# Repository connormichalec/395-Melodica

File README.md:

# 395-Melodica

Current setup, Key decoding (and to midi) on the smaller stm chip, looping jankily combined on bigger stm chip that was originally just going to be used for synthesis. Smaller ship sends midi data to synthesis. Synthesis manages looping and sends back midi data for smaller one to route to the output. TODO: Either re-seperate using a smaller chip with bigger ram (ideal). Or just get rid of smaller one together.

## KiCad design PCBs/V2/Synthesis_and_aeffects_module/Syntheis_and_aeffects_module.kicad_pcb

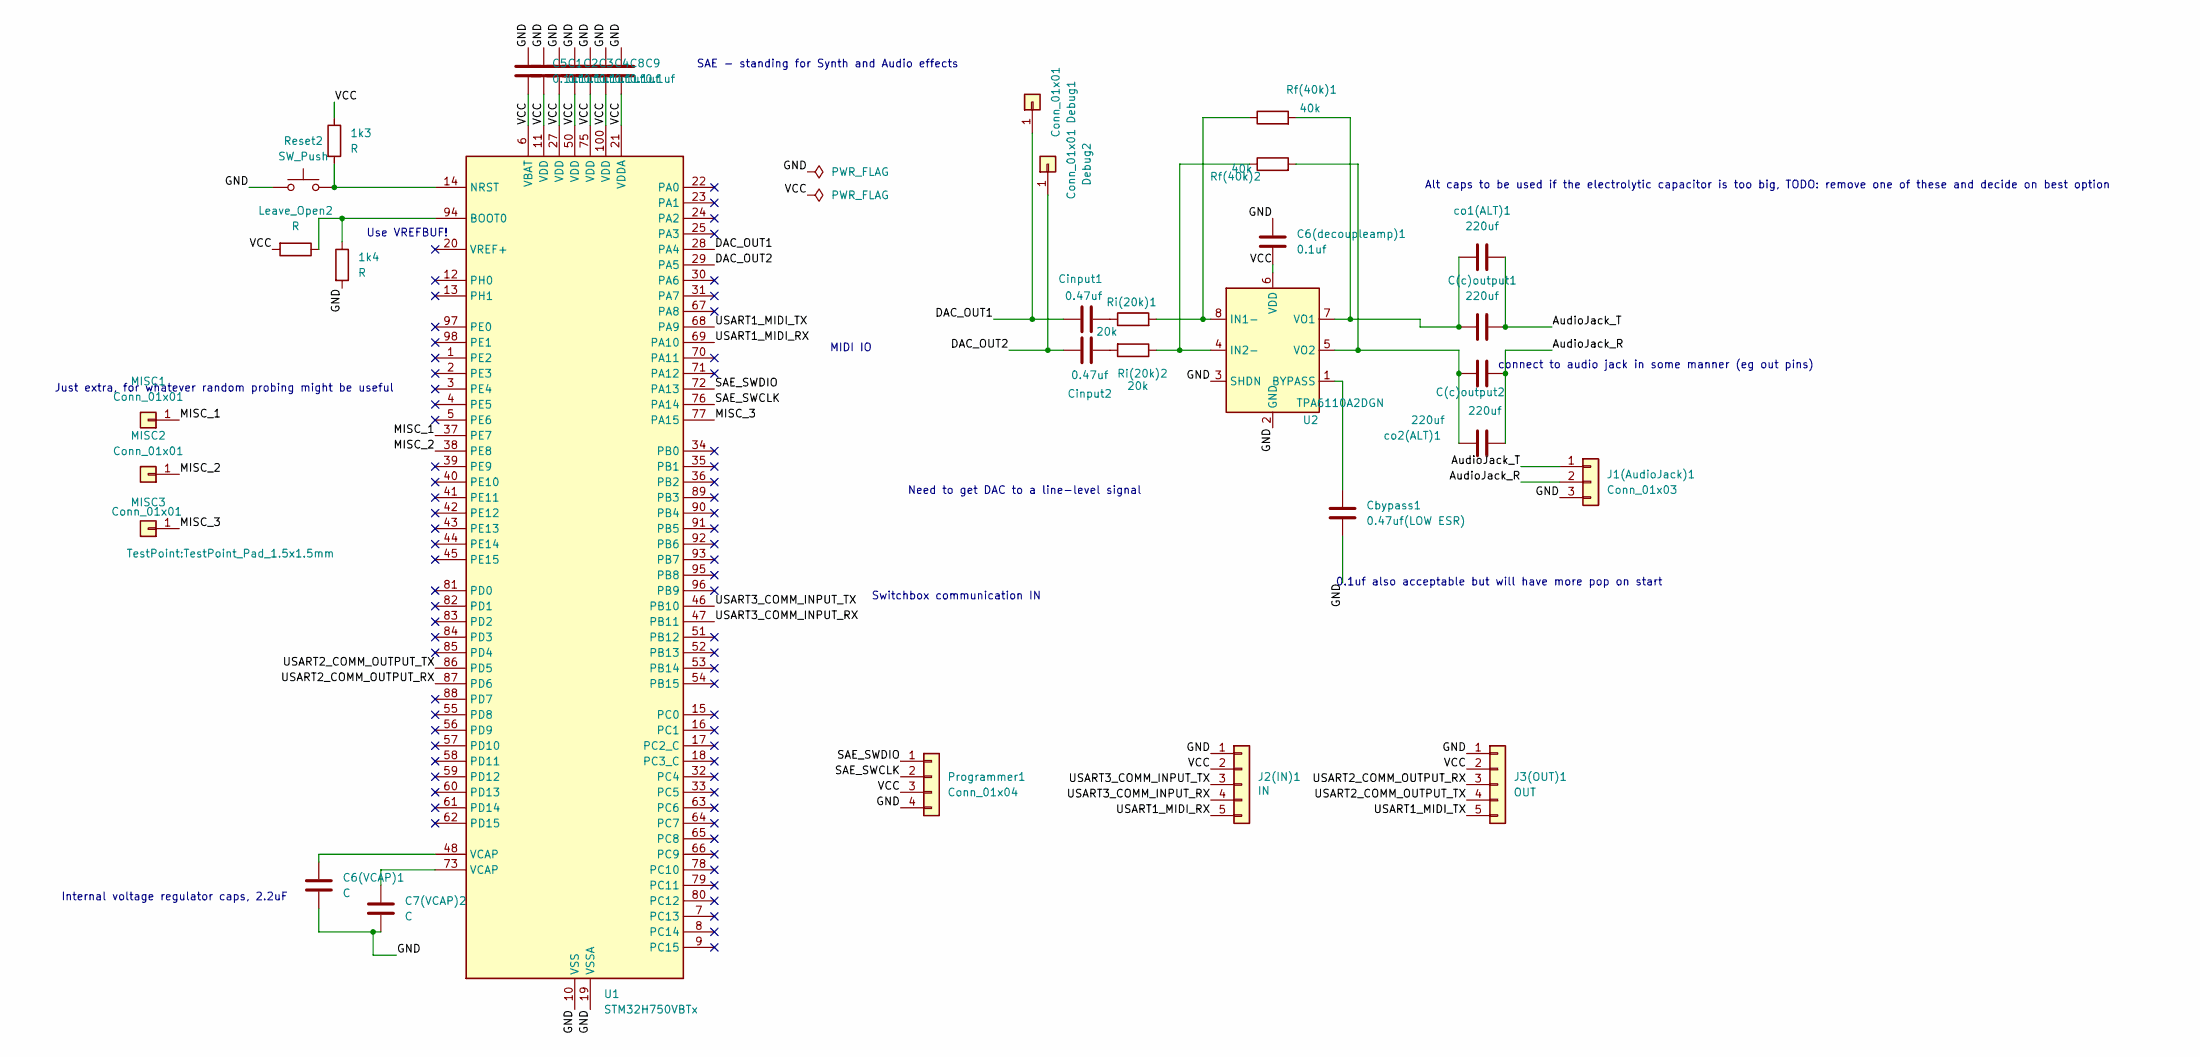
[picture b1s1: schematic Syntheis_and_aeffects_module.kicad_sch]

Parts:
1k3, 1k4: R; R_0603_1608Metric_Pad0.98x0.95mm_HandSolder
C1, C2, C3, C4, C5, C6(decoupleamp)1, C8, C9: 0.1uf; C_0603_1608Metric_Pad1.08x0.95mm_HandSolder
C6(VCAP)1, C7(VCAP)2: C; C_0603_1608Metric_Pad1.08x0.95mm_HandSolder
C(c)output1, C(c)output2: 220uf; CP_Radial_D5.0mm_P2.00mm
Cbypass1: 0.47uf(LOW ESR); C_0603_1608Metric_Pad1.08x0.95mm_HandSolder
Cinput1, Cinput2: 0.47uf; C_0603_1608Metric_Pad1.08x0.95mm_HandSolder
Debug1, Debug2: Conn_01x01; TestPoint_Pad_1.5x1.5mm
J1(AudioJack)1: Conn_01x03; PinHeader_1x03_P2.54mm_Vertical
J2(IN)1: IN; PinHeader_1x05_P2.54mm_Vertical
J3(OUT)1: OUT; PinHeader_1x05_P2.54mm_Vertical
Leave_Open2: R; R_Axial_DIN0204_L3.6mm_D1.6mm_P7.62mm_Horizontal
MISC1, MISC2, MISC3: Conn_01x01; TestPoint_Pad_1.5x1.5mm
Programmer1: Conn_01x04; PinHeader_1x04_P2.54mm_Vertical
Reset2: SW_Push; SW_PUSH_6mm_H4.3mm
Rf(40k)1, Rf(40k)2: 40k; R_Axial_DIN0207_L6.3mm_D2.5mm_P10.16mm_Horizontal
Ri(20k)1, Ri(20k)2: 20k; R_Axial_DIN0207_L6.3mm_D2.5mm_P10.16mm_Horizontal
U1: STM32H750VBTx; LQFP-100_14x14mm_P0.5mm
U2: TPA6110A2DGN; HVSSOP-8-1EP_3x3mm_P0.65mm_EP1.57x1.89mm
co1(ALT)1, co2(ALT)1: 220uf; C_1206_3216Metric_Pad1.33x1.80mm_HandSolder

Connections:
/AudioJack_R: C(c)output2.2, J1(AudioJack)1.2, co2(ALT)1.2
/AudioJack_T: C(c)output1.2, J1(AudioJack)1.1, co1(ALT)1.2
/DAC_OUT1: Cinput1.1, Debug1.1, U1.28 (PA4)
/DAC_OUT2: Cinput2.1, Debug2.1, U1.29 (PA5)
/GND: 1k4.2, C1.1, C2.1, C3.1, C4.1, C5.1, C6(VCAP)1.2, C6(decoupleamp)1.1, C7(VCAP)2.2, C8.1, C9.1, Cbypass1.2, J1(AudioJack)1.3, J2(IN)1.1, J3(OUT)1.1, Programmer1.4, Reset2.1, U1.10 (VSS), U1.19 (VSSA), U1.26 (VSS), U1.49 (VSS), U1.74 (VSS), U1.99 (VSS), U2.2 (GND), U2.3 (SHDN), U2.9 (GND)
/MISC_1: MISC1.1, U1.37 (PE7)
/MISC_2: MISC2.1, U1.38 (PE8)
/MISC_3: MISC3.1, U1.77 (PA15)
/SAE_SWCLK: Programmer1.2, U1.76 (PA14)
/SAE_SWDIO: Programmer1.1, U1.72 (PA13)
/USART1_MIDI_RX: J2(IN)1.5, U1.69 (PA10)
/USART1_MIDI_TX: J3(OUT)1.5, U1.68 (PA9)
/USART2_COMM_OUTPUT_RX: J3(OUT)1.3, U1.87 (PD6)
/USART2_COMM_OUTPUT_TX: J3(OUT)1.4, U1.86 (PD5)
/USART3_COMM_INPUT_RX: J2(IN)1.4, U1.47 (PB11)
/USART3_COMM_INPUT_TX: J2(IN)1.3, U1.46 (PB10)
/VCC: 1k3.1, C1.2, C2.2, C3.2, C4.2, C5.2, C6(decoupleamp)1.2, C8.2, C9.2, J2(IN)1.2, J3(OUT)1.2, Leave_Open2.2, Programmer1.3, U1.6 (VBAT), U1.11 (VDD), U1.21 (VDDA), U1.27 (VDD), U1.50 (VDD), U1.75 (VDD), U1.100 (VDD), U2.6 (VDD)
unnamed: C6(VCAP)1.1, U1.48 (VCAP)
unnamed: C7(VCAP)2.1, U1.73 (VCAP)
unnamed: Cinput1.2, Ri(20k)1.1
unnamed: Cinput2.2, Ri(20k)2.2
unnamed: 1k4.1, Leave_Open2.1, U1.94 (BOOT0)
unnamed: 1k3.2, Reset2.2, U1.14 (NRST)
unnamed: Cbypass1.1, U2.1 (BYPASS)
unnamed: Rf(40k)1.1, Ri(20k)1.2, U2.8 (IN1-)
unnamed: Rf(40k)2.1, Ri(20k)2.1, U2.4 (IN2-)
unnamed: C(c)output1.1, Rf(40k)1.2, U2.7 (VO1), co1(ALT)1.1
unnamed: C(c)output2.1, Rf(40k)2.2, U2.5 (VO2), co2(ALT)1.1

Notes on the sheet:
Switchbox communication IN
Need to get DAC to a line-level signal
connect to audio jack in some manner (eg out pins)
0.1uf also acceptable but will have more pop on start
SAE - standing for Synth and Audio effects
MIDI IO
Internal voltage regulator caps, 2.2uF
Alt caps to be used if the electrolytic capacitor is too big, TODO: remove one of these and decide on best option
Use VREFBUF!
Just extra, for whatever random probing might be useful

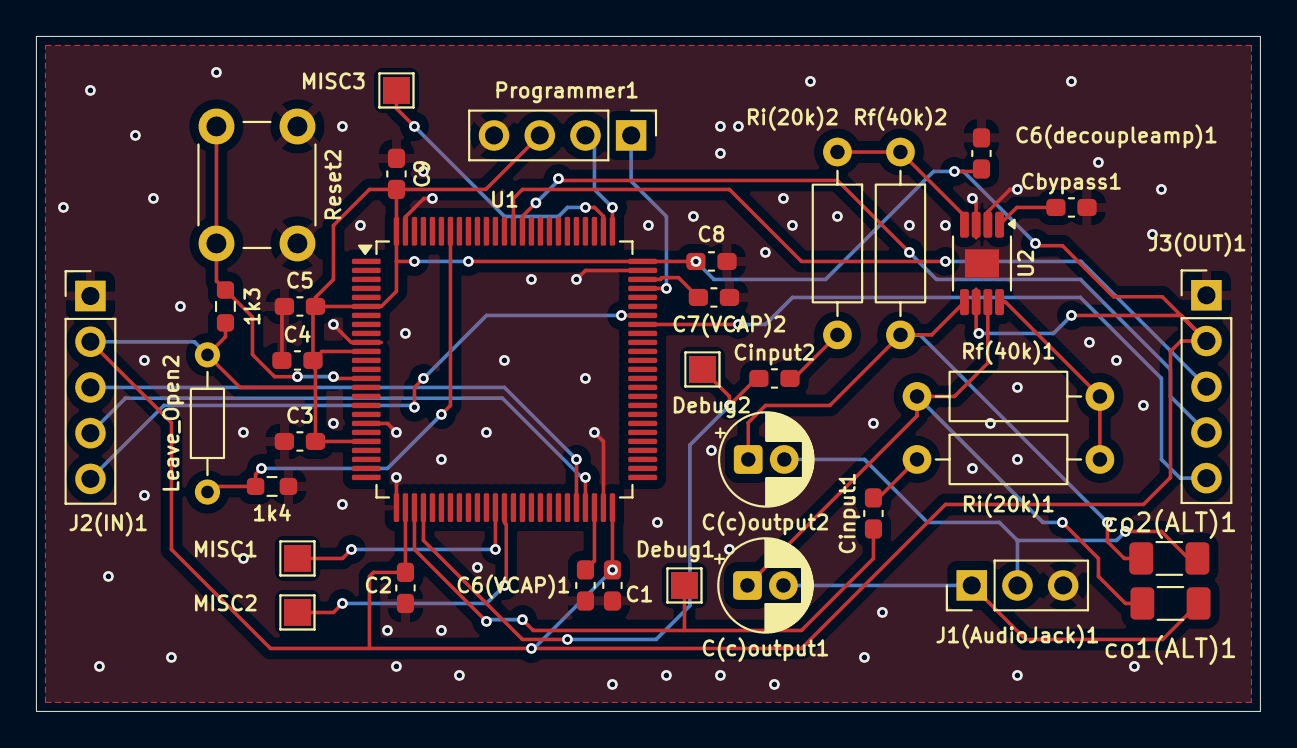
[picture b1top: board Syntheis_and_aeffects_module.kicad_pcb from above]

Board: 2 copper layers, 68.0 x 37.5 mm, 36 parts (0 on the bottom side), 28 nets.

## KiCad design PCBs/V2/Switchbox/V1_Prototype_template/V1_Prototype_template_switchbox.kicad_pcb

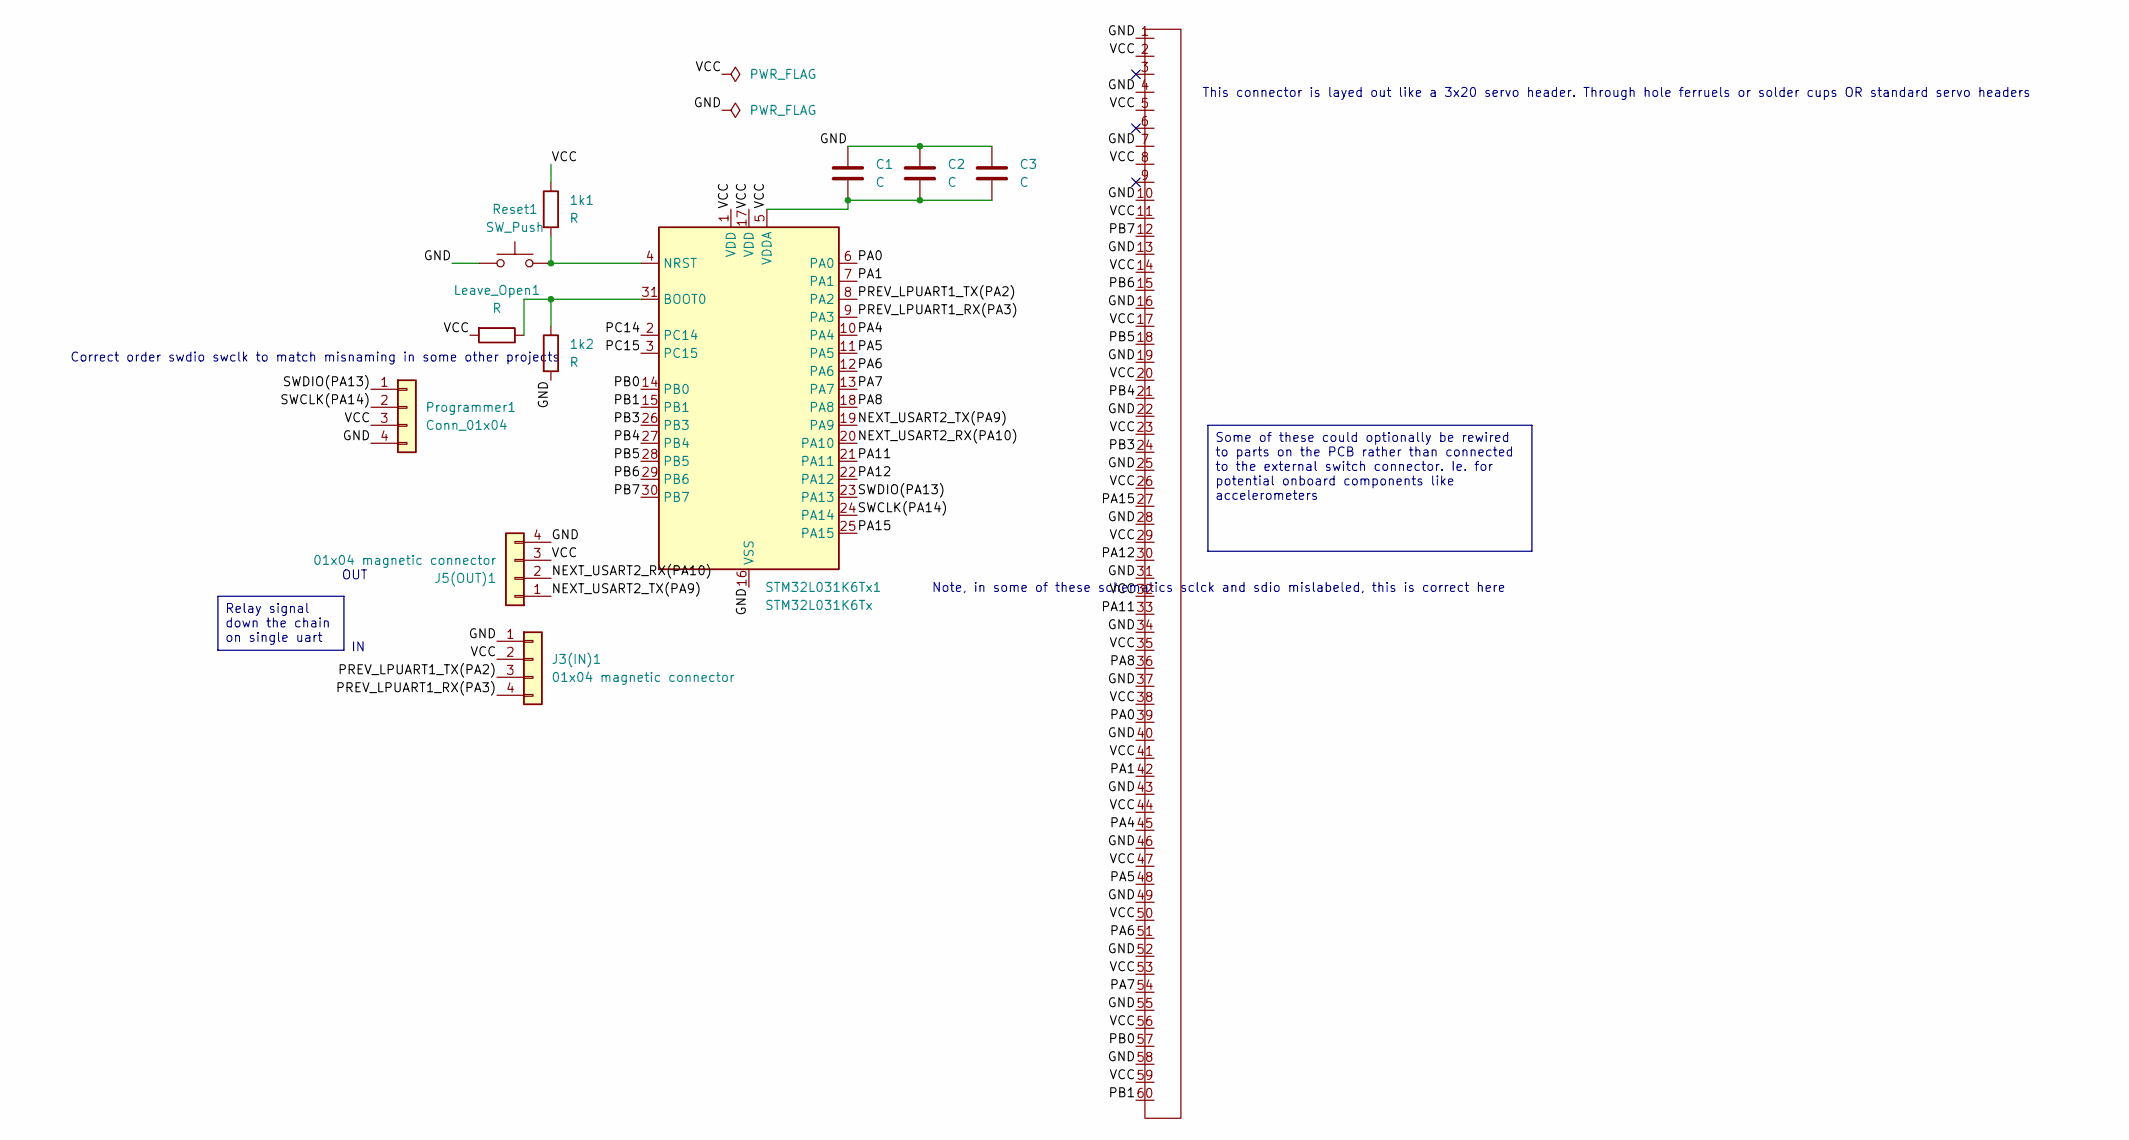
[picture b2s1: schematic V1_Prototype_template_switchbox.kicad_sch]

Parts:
1k1, 1k2: R; R_0603_1608Metric_Pad0.98x0.95mm_HandSolder
C1, C2, C3: C; C_0603_1608Metric
J3(IN)1, J5(OUT)1: 01x04 magnetic connector; 5358_4pin_connector_customfootprint
Leave_Open1: R; R_0603_1608Metric_Pad0.98x0.95mm_HandSolder
Programmer1: Conn_01x04; PinHeader_1x04_P2.54mm_Vertical
Reset1: SW_Push; SW_PUSH_6mm_H4.3mm
STM32L031K6Tx1: STM32L031K6Tx; LQFP-32_7x7mm_P0.8mm
U1: PinHeader_03x20

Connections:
/GND: 1k2.2, C1.1, C2.1, C3.1, J3(IN)1.1, J5(OUT)1.4, Programmer1.4, Reset1.1, STM32L031K6Tx1.16 (VSS), STM32L031K6Tx1.32 (VSS), U1.1, U1.4, U1.7, U1.10, U1.13, U1.16, U1.19, U1.22, U1.25, U1.28, U1.31, U1.34, U1.37, U1.40, U1.43, U1.46, U1.49, U1.52, U1.55, U1.58
/NEXT_USART2_RX(PA10): J5(OUT)1.2, STM32L031K6Tx1.20 (PA10)
/NEXT_USART2_TX(PA9): J5(OUT)1.1, STM32L031K6Tx1.19 (PA9)
/PA0: STM32L031K6Tx1.6 (PA0), U1.39
/PA1: STM32L031K6Tx1.7 (PA1), U1.42
/PA4: STM32L031K6Tx1.10 (PA4), U1.45
/PA5: STM32L031K6Tx1.11 (PA5), U1.48
/PA6: STM32L031K6Tx1.12 (PA6), U1.51
/PA7: STM32L031K6Tx1.13 (PA7), U1.54
/PA8: STM32L031K6Tx1.18 (PA8), U1.36
/PA11: STM32L031K6Tx1.21 (PA11), U1.33
/PA12: STM32L031K6Tx1.22 (PA12), U1.30
/PA15: STM32L031K6Tx1.25 (PA15), U1.27
/PB0: STM32L031K6Tx1.14 (PB0), U1.57
/PB1: STM32L031K6Tx1.15 (PB1), U1.60
/PB3: STM32L031K6Tx1.26 (PB3), U1.24
/PB4: STM32L031K6Tx1.27 (PB4), U1.21
/PB5: STM32L031K6Tx1.28 (PB5), U1.18
/PB6: STM32L031K6Tx1.29 (PB6), U1.15
/PB7: STM32L031K6Tx1.30 (PB7), U1.12
/PC14: STM32L031K6Tx1.2 (PC14)
/PC15: STM32L031K6Tx1.3 (PC15)
/PREV_LPUART1_RX(PA3): J3(IN)1.4, STM32L031K6Tx1.9 (PA3)
/PREV_LPUART1_TX(PA2): J3(IN)1.3, STM32L031K6Tx1.8 (PA2)
/SWCLK(PA14): Programmer1.2, STM32L031K6Tx1.24 (PA14)
/SWDIO(PA13): Programmer1.1, STM32L031K6Tx1.23 (PA13)
/VCC: 1k1.1, C1.2, C2.2, C3.2, J3(IN)1.2, J5(OUT)1.3, Leave_Open1.2, Programmer1.3, STM32L031K6Tx1.1 (VDD), STM32L031K6Tx1.5 (VDDA), STM32L031K6Tx1.17 (VDD), U1.2, U1.5, U1.8, U1.11, U1.14, U1.17, U1.20, U1.23, U1.26, U1.29, U1.32, U1.35, U1.38, U1.41, U1.44, U1.47, U1.50, U1.53, U1.56, U1.59
unnamed: 1k2.1, Leave_Open1.1, STM32L031K6Tx1.31 (BOOT0)
unnamed: 1k1.2, Reset1.2, STM32L031K6Tx1.4 (NRST)

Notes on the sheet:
Note, in some of these schematics sclck and sdio mislabeled, this is correct here
This connector is layed out like a 3x20 servo header. Through hole ferruels or solder cups OR standard servo headers
OUT
Correct order swdio swclk to match misnaming in some other projects
Relay signal down the chain on single uart
Some of these could optionally be rewired to parts on the PCB rather than connected to the external switch connector. Ie. for potential onboard components like accelerometers

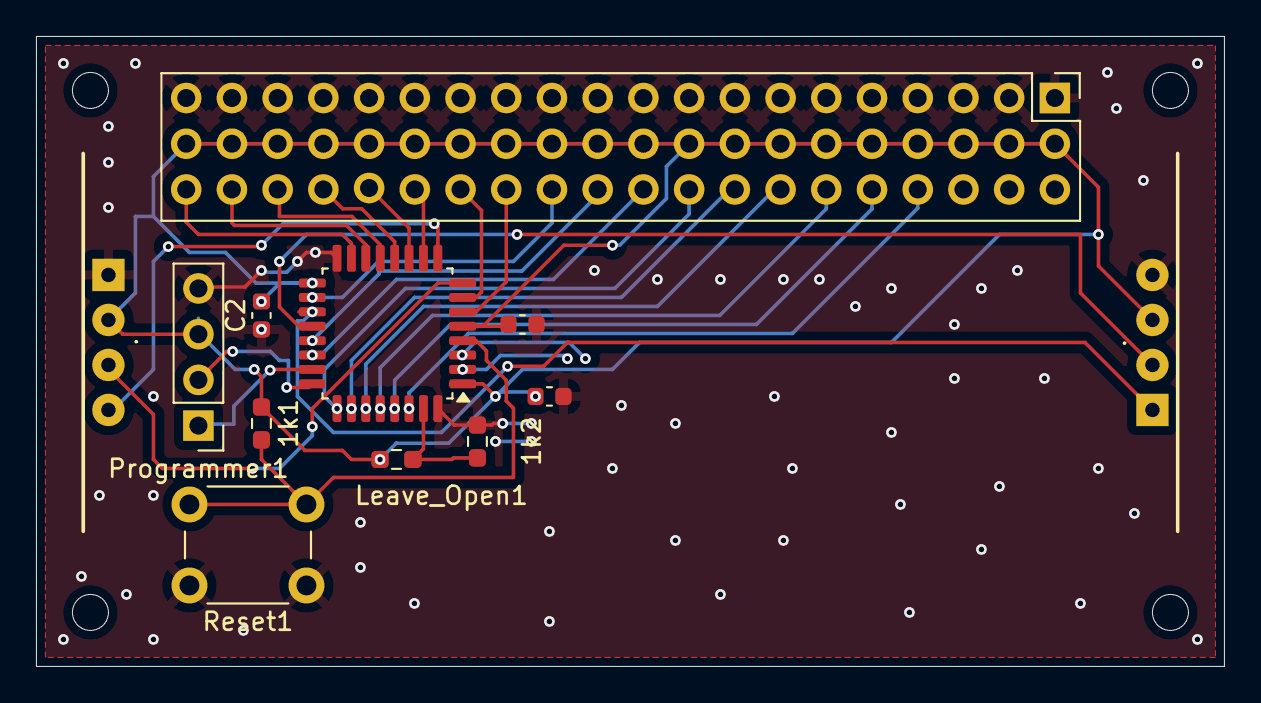
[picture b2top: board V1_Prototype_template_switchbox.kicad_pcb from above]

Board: 2 copper layers, 66.0 x 35.0 mm, 12 parts (0 on the bottom side), 27 nets.

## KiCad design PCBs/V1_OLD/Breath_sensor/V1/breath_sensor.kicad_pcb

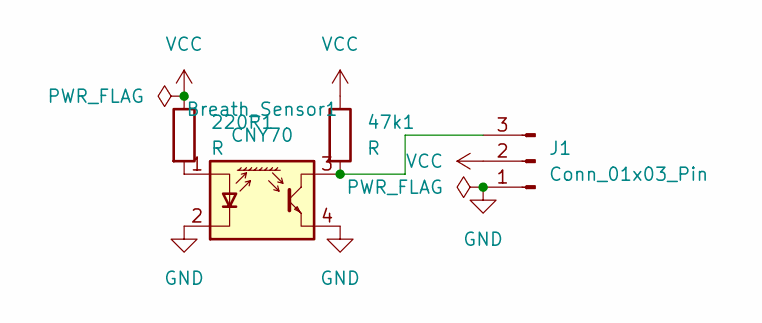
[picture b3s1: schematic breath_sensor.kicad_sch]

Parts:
47k1, 220R1: R; R_Axial_DIN0204_L3.6mm_D1.6mm_P7.62mm_Horizontal
Breath_Sensor1: CNY70; Vishay_CNY70
J1: Conn_01x03_Pin; PinHeader_1x03_P2.54mm_Horizontal

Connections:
GND: Breath_Sensor1.2 (K), Breath_Sensor1.4 (E), J1.1
unnamed: 220R1.2, Breath_Sensor1.1 (A)
unnamed: 47k1.2, Breath_Sensor1.3 (C), J1.3
VCC: 47k1.1, 220R1.1, J1.2

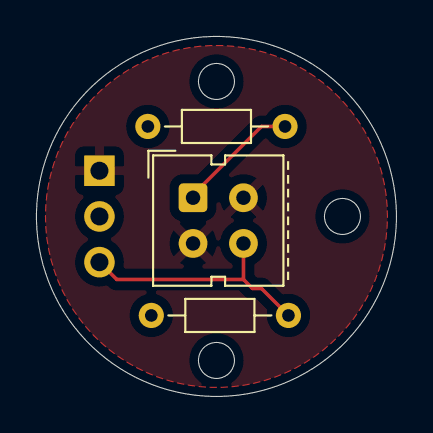
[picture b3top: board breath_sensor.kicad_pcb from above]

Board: 2 copper layers, 20.0 x 20.0 mm, 4 parts (0 on the bottom side), 4 nets.

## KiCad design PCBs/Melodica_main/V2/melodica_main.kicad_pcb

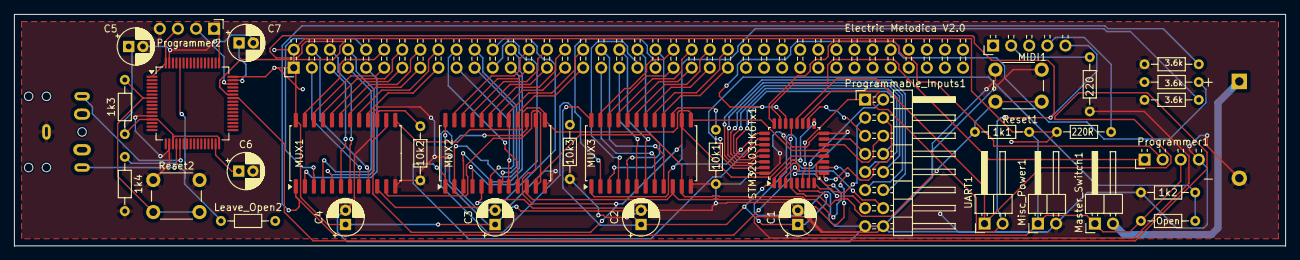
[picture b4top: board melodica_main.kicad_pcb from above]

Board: 2 copper layers, 178.5 x 32.5 mm, 38 parts (0 on the bottom side), 91 nets.

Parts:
1k1, 1k2, 1k3, 1k4, 3.6k, 3.6k#2, 3.6k#3, 10k1, 10k2, 10k3, 220, 220R: R; R_Axial_DIN0204_L3.6mm_D1.6mm_P7.62mm_Horizontal
BT1: Battery; BatteryHolder_MPD_BC2AAPC_2xAA
C1, C2, C3, C4, C5, C6, C7: C; CP_Radial_D5.0mm_P2.00mm
J1: AudioJack3_SwitchTR; Jack_3.5mm_CUI_SJ1-3525N_Horizontal
Keys1: Conn_02x38_Odd_Even_Shielded; PinHeader_2x38_P2.54mm_Horizontal
Leave_Open2: R; R_Axial_DIN0204_L3.6mm_D1.6mm_P7.62mm_Horizontal
MIDI1: Conn_01x05; PinHeader_1x05_P2.54mm_Horizontal
MUX1, MUX2, MUX3: CD74HC4067M; SOIC-24W_7.5x15.4mm_P1.27mm
Master_Switch1: Conn_01x02; PinHeader_1x02_P2.54mm_Horizontal
Misc_Power1: Conn_01x02; PinHeader_1x02_P2.54mm_Horizontal
Open: R; R_Axial_DIN0204_L3.6mm_D1.6mm_P7.62mm_Horizontal
Programmable_Inputs1: Conn_02x08_Odd_Even; PinHeader_2x08_P2.54mm_Horizontal
Programmer1, Programmer2: Conn_01x04; PinHeader_1x04_P2.54mm_Horizontal
Reset1, Reset2: SW_Push; SW_PUSH_6mm_H4.3mm
STM32L031K6Tx1: STM32L031K6Tx; LQFP-32_7x7mm_P0.8mm
U1: STM32F405RGTx; LQFP-64_10x10mm_P0.5mm
UART1: Conn_01x02_Pin; PinHeader_1x02_P2.54mm_Horizontal

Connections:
/DAC1_SYNTH: J1.T, U1.20 (PA4)
/DAC2_SYNTH: J1.R, U1.21 (PA5)
/IN_0: 3.6k.2, MUX1.1 (COM), STM32L031K6Tx1.21 (PA11)
/IN_1: 3.6k#2.1, MUX2.1 (COM), STM32L031K6Tx1.22 (PA12)
/IN_2: 3.6k#3.2, MUX3.1 (COM), STM32L031K6Tx1.25 (PA15)
/N0: Keys1.4, MUX1.9 (I0)
/N1: Keys1.3, MUX1.8 (I1)
/N2: Keys1.6, MUX1.7 (I2)
/N3: Keys1.5, MUX1.6 (I3)
/N4: Keys1.8, MUX1.5 (I4)
/N5: Keys1.7, MUX1.4 (I5)
/N6: Keys1.10, MUX1.3 (I6)
/N7: Keys1.9, MUX1.2 (I7)
/N8: Keys1.12, MUX1.23 (I8)
/N9: Keys1.11, MUX1.22 (I9)
/N10: Keys1.14, MUX1.21 (I10)
/N11: Keys1.13, MUX1.20 (I11)
/N12: Keys1.16, MUX1.19 (I12)
/N13: Keys1.15, MUX1.18 (I13)
/N14: Keys1.18, MUX1.17 (I14)
/N15: Keys1.17, MUX1.16 (I15)
/N16: Keys1.20, MUX2.9 (I0)
/N17: Keys1.19, MUX2.8 (I1)
/N18: Keys1.22, MUX2.7 (I2)
/N19: Keys1.21, MUX2.6 (I3)
/N20: Keys1.24, MUX2.5 (I4)
/N21: Keys1.23, MUX2.4 (I5)
/N22: Keys1.26, MUX2.3 (I6)
/N23: Keys1.25, MUX2.2 (I7)
/N24: Keys1.28, MUX2.23 (I8)
/N25: Keys1.27, MUX2.22 (I9)
/N26: Keys1.30, MUX2.21 (I10)
/N27: Keys1.29, MUX2.20 (I11)
/N28: Keys1.32, MUX2.19 (I12)
/N29: Keys1.31, MUX2.18 (I13)
/N30: Keys1.34, MUX2.17 (I14)
/N31: Keys1.33, MUX2.16 (I15)
/N32: Keys1.36, MUX3.9 (I0)
/N33: Keys1.35, MUX3.8 (I1)
/N34: Keys1.38, MUX3.7 (I2)
/N35: Keys1.37, MUX3.6 (I3)
/N36: Keys1.40, MUX3.5 (I4)
/N37: Keys1.39, MUX3.4 (I5)
/N38: Keys1.42, MUX3.3 (I6)
/N39: Keys1.41, MUX3.2 (I7)
/N40: Keys1.44, MUX3.23 (I8)
/N41: Keys1.43, MUX3.22 (I9)
/N42: Keys1.46, MUX3.21 (I10)
/N43: Keys1.45, MUX3.20 (I11)
/N44: Keys1.48, MUX3.19 (I12)
/N45: Keys1.47, MUX3.18 (I13)
/N46: Keys1.50, MUX3.17 (I14)
/N47: Keys1.49, MUX3.16 (I15)
/PA0: Programmable_Inputs1.1, STM32L031K6Tx1.6 (PA0)
/PA1: Programmable_Inputs1.2, STM32L031K6Tx1.7 (PA1)
/PA2: Programmable_Inputs1.3, STM32L031K6Tx1.8 (PA2)
/PA3: Programmable_Inputs1.4, STM32L031K6Tx1.9 (PA3)
/PA8: Programmable_Inputs1.5, STM32L031K6Tx1.18 (PA8)
/PB0: Programmable_Inputs1.6, STM32L031K6Tx1.14 (PB0)
/PB1: Programmable_Inputs1.7, STM32L031K6Tx1.15 (PB1)
/PB3: Programmable_Inputs1.8, STM32L031K6Tx1.26 (PB3)
/PB4: Programmable_Inputs1.9, STM32L031K6Tx1.27 (PB4)
/PB5: Programmable_Inputs1.10, STM32L031K6Tx1.28 (PB5)
/PB6: Programmable_Inputs1.11, STM32L031K6Tx1.29 (PB6)
/PB7: Programmable_Inputs1.12, STM32L031K6Tx1.30 (PB7)
/PC14: Programmable_Inputs1.13, STM32L031K6Tx1.2 (PC14)
/PC15: Programmable_Inputs1.14, STM32L031K6Tx1.3 (PC15)
/S0: MUX1.10 (S0), MUX2.10 (S0), MUX3.10 (S0), STM32L031K6Tx1.10 (PA4)
/S1: MUX1.11 (S1), MUX2.11 (S1), MUX3.11 (S1), STM32L031K6Tx1.11 (PA5)
/S2: MUX1.14 (S2), MUX2.14 (S2), MUX3.14 (S2), STM32L031K6Tx1.12 (PA6)
/S3: MUX1.13 (S3), MUX2.13 (S3), MUX3.13 (S3), STM32L031K6Tx1.13 (PA7)
/SWCLK_MAIN: Programmer1.1, STM32L031K6Tx1.23 (PA13)
/SWCLK_SYNTH: Programmer2.1, U1.49 (PA14)
/SWDIO_MAIN: Programmer1.2, STM32L031K6Tx1.24 (PA14)
/SWDIO_SYNTH: Programmer2.2, U1.46 (PA13)
/UART_RX_MAIN: STM32L031K6Tx1.20 (PA10), U1.42 (PA9), UART1.1
/UART_RX_SYNTH: MIDI1.5, STM32L031K6Tx1.19 (PA9), U1.43 (PA10), UART1.2
GND: 1k2.2, 1k4.2, 3.6k.1, 3.6k#2.2, 3.6k#3.1, 10k1.2, 10k2.1, 10k3.2, 220.1, BT1.2 (-), C1.2, C2.2, C3.2, C4.2, C5.2, C6.2, C7.2, J1.S, MUX1.12 (GND), MUX2.12 (GND), MUX3.12 (GND), Misc_Power1.2, Programmable_Inputs1.15, Programmable_Inputs1.16, Programmer1.4, Programmer2.4, Reset1.1, Reset2.1, STM32L031K6Tx1.16 (VSS), STM32L031K6Tx1.32 (VSS), U1.12 (VSSA), U1.18 (VSS), U1.63 (VSS)
unnamed: BT1.1 (+), Master_Switch1.2
unnamed: 220.2, MIDI1.2
unnamed: 220R.2, MIDI1.4
unnamed: 10k2.2, MUX1.15 (~E)
unnamed: 10k3.1, MUX2.15 (~E)
unnamed: 10k1.1, MUX3.15 (~E)
unnamed: 1k2.1, Open.1, STM32L031K6Tx1.31 (BOOT0)
unnamed: 1k1.2, Reset1.2, STM32L031K6Tx1.4 (NRST)
unnamed: 1k4.1, Leave_Open2.1, U1.60 (BOOT0)
unnamed: 1k3.2, Reset2.2, U1.7 (NRST)
unnamed: C6.1, U1.31 (VCAP_1)
unnamed: C7.1, U1.47 (VCAP_2)
VCC: 1k1.1, 1k3.1, 220R.1, C1.1, C2.1, C3.1, C4.1, C5.1, Keys1.1, Keys1.2, Leave_Open2.2, MUX1.24 (VCC), MUX2.24 (VCC), MUX3.24 (VCC), Master_Switch1.1, Misc_Power1.1, Open.2, Programmer1.3, Programmer2.3, STM32L031K6Tx1.1 (VDD), STM32L031K6Tx1.5 (VDDA), STM32L031K6Tx1.17 (VDD), U1.1 (VBAT), U1.13 (VDDA), U1.19 (VDD), U1.32 (VDD), U1.48 (VDD), U1.64 (VDD)

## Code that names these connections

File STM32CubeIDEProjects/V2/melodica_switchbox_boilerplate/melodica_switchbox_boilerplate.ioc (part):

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Mcu.Name=STM32L031K(4-6)Tx
Mcu.Package=LQFP32
Mcu.UserName=STM32L031K6Tx
PA0-CK_IN.GPIOParameters=GPIO_PuPd
PA0-CK_IN.GPIO_PuPd=GPIO_PULLDOWN
PA0-CK_IN.Signal=GPIO_Input
PA1.GPIOParameters=GPIO_PuPd
PA1.GPIO_PuPd=GPIO_PULLDOWN
PA1.Signal=GPIO_Input
PA10.GPIOParameters=GPIO_Label
PA10.GPIO_Label=NEXT_RX
PA10.Mode=Asynchronous
PA10.Signal=USART2_RX
PA11.GPIOParameters=GPIO_PuPd
PA11.GPIO_PuPd=GPIO_PULLDOWN
PA11.Signal=GPIO_Input
PA12.GPIOParameters=GPIO_PuPd
PA12.GPIO_PuPd=GPIO_PULLDOWN
PA12.Signal=GPIO_Input
PA13.Mode=Serial_Wire
PA13.Signal=SYS_SWDIO
PA14.Mode=Serial_Wire
PA14.Signal=SYS_SWCLK
PA15.GPIOParameters=GPIO_PuPd
PA15.GPIO_PuPd=GPIO_PULLDOWN
PA15.Signal=GPIO_Input
PA2.GPIOParameters=GPIO_Label
PA2.GPIO_Label=PREX_TX
PA2.Mode=Asynchronous
PA2.Signal=LPUART1_TX
PA3.GPIOParameters=GPIO_Label
PA3.GPIO_Label=PREV_RX
PA3.Mode=Asynchronous
PA3.Signal=LPUART1_RX
PA4.Signal=GPIO_Output
PA5.Signal=SharedAnalog_PA5
PA6.Signal=SharedAnalog_PA6
PA7.Signal=SharedAnalog_PA7
PA8.GPIOParameters=GPIO_PuPd
PA8.GPIO_PuPd=GPIO_PULLDOWN
PA8.Signal=GPIO_Input
PA9.GPIOParameters=GPIO_Label
PA9.GPIO_Label=NEXT_TX
PA9.Mode=Asynchronous
PA9.Signal=USART2_TX
PB0.Signal=SharedAnalog_PB0
PB1.Signal=SharedAnalog_PB1
PB3.GPIOParameters=GPIO_PuPd
PB3.GPIO_PuPd=GPIO_PULLDOWN
PB3.Signal=GPIO_Input
PB4.GPIOParameters=GPIO_PuPd
PB4.GPIO_PuPd=GPIO_PULLDOWN
PB4.Signal=GPIO_Input
PB5.GPIOParameters=GPIO_PuPd
PB5.GPIO_PuPd=GPIO_PULLDOWN
PB5.Signal=GPIO_Input
PB6.GPIOParameters=GPIO_PuPd
PB6.GPIO_PuPd=GPIO_PULLDOWN
PB6.Signal=GPIO_Input
PB7.GPIOParameters=GPIO_PuPd
PB7.GPIO_PuPd=GPIO_PULLDOWN
PB7.Signal=GPIO_Input
RCC.HSE_VALUE=8000000
RCC.SYSCLKFreq_VALUE=2097000
board=custom

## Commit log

2025-03-01 proj setup
2025-03-03 updated Proj
2025-03-05 32-note functionality
    Got all 32 notes working
2025-03-24 update gitignore
2025-03-24 Remove unnecessary files
2025-03-24 Update project wthn folders
2025-03-25 create melodica_synthesis project
2025-03-28 Adjusting main.c to support adc
2025-03-28 More ADC stuff
2025-03-31 Breath sensor working
2025-04-01 Basic MIDI Reception
2025-04-02 MIDI Rx stuff and organ stop fix
2025-04-03 Begin work with building a synthesis system
2025-04-04 synthesis progress, sawtooth wave, switched to a circular buffer
2025-04-04 Great progess on Synthesis, cleanwaveform using circular buffer and simple oscillator system built
2025-04-08 add pcb files
2025-04-08 Some looper stuff
2025-04-08 MIDI to frequency conversion
2025-04-09 V2 PCB schematic done - added new synthesis STMF405
2025-04-10 V2 PCB design of melodica
2025-04-10 Continiued implementation of signal processing chain, implemented basic keyboard functionality, untested and needs to be refined. ADSR began implementation but needs redesign
2025-04-11 Some progress
2025-04-15 Good progress with synthesis, MIDI reception now works seamlessly. Big problem with DMA, potential race conditoins on filling buffer because randomly freezes up
2025-04-15 Basic looper stuff working!
2025-04-16 YAY! Hard fault issue was resolved by disabling interrupts temporarily (should eventually be replaced by a more professional soluiton), keyboard now works well!
2025-04-16 Some looper stuff (incomplete)
2025-04-16 Implement a voices system, better structure with multi-oscilator support
2025-04-21 More looper stuff
2025-04-22 No longer crashes when number of oscillators is exceeded!
2025-04-22 Basic linear ADSRs implemented, some performance issues though
2025-04-23 ADSR performance issues fixed, incorported key tracking into voices instead of signal, double hit key retriggers note
2025-04-27 basic logarithmic pressure control
2025-04-29 Looper pretty much done
2025-04-29 progress
2025-04-29 converted synthesis main loop to a tick based system
2025-04-29 Changed how note pressure is handled to make more efficient
2025-04-29 Detune control implemented
2025-04-30 Added low pass filters, (resonance is buggin
2025-04-30 Change Build options to Optimize fast (-Ofast) to significantly increase performance
2025-04-30 added minimum to synth cutoff on the breath pressure demo
2025-04-30 modify adsr voice creation
2025-05-03 adjust num voices/osc
2025-05-03 added debouncers for keys!
2025-05-03 small tweaks
2025-05-05 Voice channel pressures
2025-05-05 Looper loops once more
2025-05-05 Looper half working on synthesis chip
2025-05-05 Looper work!
    Notes:
    - It lags quite a bit (not good)
2025-05-06 Upload STL
2025-05-06 Buffer size changed for perfomrnace
2025-05-06 Auto-layering and reduce buffer size
2025-09-02 Added V2 schematic.drawio
2025-09-02 cleanup
2025-09-09 created melodica cad file and started editing
2025-09-09 F and E keys done
2025-09-10 Melodica Cad update - all white keys done
2025-09-16 Keys done, progress made on starting base of melodica
2025-09-30 base model done
2025-09-30 Progress on Case design for CAD, start on switchbox schematic
2025-09-30 some progress on switchbox schematic
2025-10-01 progress on switchboard schematic
2025-10-02 good progress on switchbox pcb design
2025-10-07 PCB For switchbox prototype done
2025-10-07 fixed connector heights on switchbox pcb
2025-10-07 small fixes to switchbox pcb
2025-10-10 reorginization, started progess on synth_aeffects pcb
2025-10-11 CAD progress
2025-10-14 pcb progress
2025-10-15 schematic progress
2025-10-15 add meloica_looper stm32 project
2025-10-15 remove adiojack from schematic, replace with pin headers
2025-10-15 more progress on synthesis pcb
2025-10-17 some updates
2025-10-21 Kobe Update files
2025-10-21 messed UART connection for synthesis PCB :/ good thing i had those misc pads for testing. Need to reorder.
2025-10-21 Switchbox pcb was also fucked up, fixed that, need to order now. (and tweaked the switchbox boilerplate code.
2025-10-22 some configurations
2025-10-23 Began implementation of control states for synthesis, we need a system to keep track of settings and allow updating those values based on switchbox input
2025-10-24 Progress on synthesis module, added support for changing voices on the fly
2025-10-24 some small changes
2025-10-29 testing and fixing PCBs, reordered
2025-11-02 synthesis operational
2025-11-04 some updates for switchbox
2025-11-04 ch-ch-ch changeeeesss
2025-11-04 Progess with switchbox code
2025-11-05 Remove design note for STMF405 in audio.c
2025-11-06 IO Switchbox code implementation updates
2025-11-07 implemented initialization polling function for connectivity
2025-11-08 Added a misc struct to io object, allows passing of misc data to polling functions; also implemented a test design for 3 switches
2025-11-08 began implementation of potetiometers for switchbox
2025-11-08 some implementation on updating parameters especially with pots as fixed point representations to send over uart
2025-11-08 throw device id in there
2025-11-09 Progress on fx chip, Rx still not working
2025-11-13 bugfix
2025-11-13 Starting new connectivity format
2025-11-17 added more parameter handling
2025-11-18 Working on switchbox stuff
2025-11-18 Attempting to fix switchbox rx
2025-11-19 toggle test works
2025-11-19 some tests with switchbox->synth connectivity, seems basic connection is working
2025-11-20 Prepping for merge
2025-11-20 Fixing up issues with protocol
2025-11-20 Fixing module rx on midifx board
2025-12-01 Basic switchbox functionality tests with Synthesis, 3 way switch works! is able to select oscillator type
2025-12-03 Potentiometer works!
2025-12-05 all switches/pots implementedgit add .!
2025-12-09 System now (actually) sends an initial update when first powered on - fixed issue because sending a bunch of parameters one after another overloads synth receiver and it only updates the first
2025-12-09 changed some interrupt NVIC priorities (hopefully reduce pot crackling)
2025-12-09 basic breath sensing working - some jankiness with setup tho need to fix
